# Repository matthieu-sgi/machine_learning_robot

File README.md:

# Machine learning robot

The machine learning bot is a project of making an OpenSource robot that will be able to learn from its environment and adapt to it using machine learning.

The robot is based on a FREENOVE ESP32 S3 MCU and its camera. It also includes a LIDAR.
The mechanical part is based on a Adafruit 3216 chassis.

## Electronics

### Electronics components

The robot is based on a [FREENOVE ESP32 S3](https://github.com/Freenove/Freenove_ESP32_S3_WROOM_Board).

In addition to the included camera, we bought [this camera](https://www.amazon.fr/gp/product/B0BXSL76L8/ref=ewc_pr_img_1?smid=AFDYUAFSP3DOA&psc=1). The ribbon cable is longer than the included one and it allows to position it on the front of the robot.

The LIDAR used is a LD06 from innomaker ([datasheet](https://www.inno-maker.com/wp-content/uploads/2020/11/LDROBOT_LD06_Datasheet.pdf)).

### PCB

The chassis chosen is very tiny. It includes only two frame for two stages. To gain space, we decided to build and make a full PCB stage. Allowing the robot to go from 2 to 3 stages.

The PCB project can be found in the [pcb](https://github.com/matthieu-sgi/machine_learning_robot/tree/main/PCB) folder.

3D view of the PCB:

Front 3D view | Back 3D view
:------------:|:------------:
 |

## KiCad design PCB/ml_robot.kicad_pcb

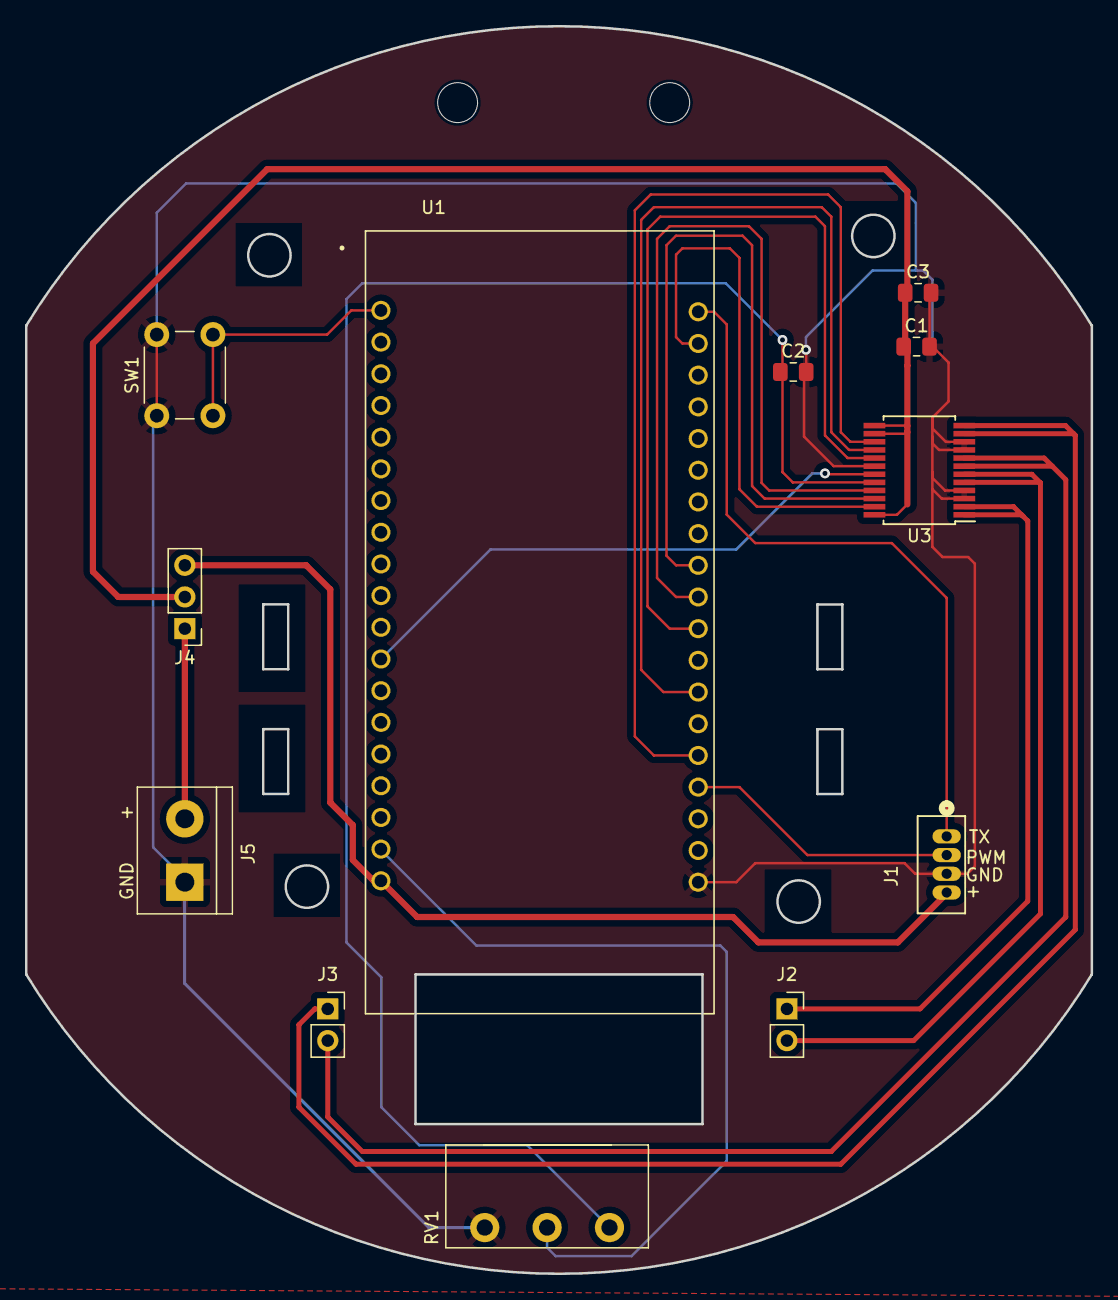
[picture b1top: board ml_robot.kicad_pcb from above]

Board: 2 copper layers, 85.4 x 100.0 mm, 12 parts (0 on the bottom side), 20 nets.

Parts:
C1: 10u; C_0805_2012Metric_Pad1.18x1.45mm_HandSolder
C2, C3: 100nF; C_0805_2012Metric_Pad1.18x1.45mm_HandSolder
J1: lidar_conn; CONN_B4B-ZR_LF__SN__JST
J2: Motor1; PinSocket_1x02_P2.54mm_Vertical
J3: Motor2; PinSocket_1x02_P2.54mm_Vertical
J4: jmp_alim; PinHeader_1x03_P2.54mm_Vertical
J5: ext_power; TerminalBlock_bornier-2_P5.08mm
RV1: 100kΩ; Potentiometer_Piher_PC-16_Single_Horizontal
SW1: SW_Push; SW_PUSH_6mm
U1: ESP32-S3-DEVKITC-1-N8R2; XCVR_ESP32-S3-DEVKITC-1-N8R2
U3: TB6612FNG; SSOP-24_5.3x8.2mm_P0.65mm

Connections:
+3V3: C2.1, RV1.1, U3.20 (VCC)
+5V: J1.4, J4.3, U1.J1_21 (5V0)
/PWM_motor_A: U1.J3_4 (GPIO1), U3.23 (PWMA)
/PWM_motor_B: U1.J3_17 (GPIO47), U3.15 (PWMB)
/STBY_motor: U1.J1_14 (GPIO46), U3.19 (STBY)
/control_M1_A: U1.J3_12 (GPIO36), U3.21 (AIN1)
/control_M1_B: U1.J3_11 (GPIO37), U3.22 (AIN2)
/control_M2_A: U1.J3_15 (GPIO45), U3.16 (BIN2)
/control_M2_B: U1.J3_13 (GPIO35), U3.17 (BIN1)
/lidar_pwm: J1.2, U1.J3_18 (GPIO21)
/lidar_tx: J1.1, U1.J3_3 (U0RXD/GPIO44)
/v_motor: C1.1, C3.1, J4.2, U3.13 (VM2), U3.14 (VM3), U3.24 (VM1)
GND: C1.2, C2.2, C3.2, J1.3, J5.1, RV1.3, SW1.1, U1.J3_21 (GND), U3.3 (PGND1), U3.4 (PGND1), U3.9 (PGND2), U3.10 (PGND2), U3.18 (GND)
unnamed: J2.1, U3.1 (AO1), U3.2 (AO1)
unnamed: J2.2, U3.5 (AO2), U3.6 (AO2)
unnamed: J3.1, U3.11 (BO1), U3.12 (BO1)
unnamed: J3.2, U3.7 (BO2), U3.8 (BO2)
unnamed: RV1.2, U1.J1_20 (GPIO14)
unnamed: SW1.2, U1.J1_3 (RST)
VCC: J4.1, J5.2

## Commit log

2023-10-05 Adding PCB design
2023-10-05 Adding exclusion zones
2023-10-05 Changing README
2023-10-05 Adding media for README
2023-10-11 PCB version to fab
2023-10-11 Adding platform mechanical schematic
2024-12-18 Add doc
